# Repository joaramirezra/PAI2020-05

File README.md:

# Proyecto Respirador unal
**Version :** 1.0

**Descripcion :** Durante la epidemia del covid-19, el mundo afronta un sin fin de desafios entre ellos el preservar la mayor cantidad de vidas posibles,Esta infeccion suelen contar con fiebre y síntomas respiratorios (tos y disnea o dificultad para respirar). En los casos más graves, pueden causar neumonía, síndrome respiratorio agudo severo, insuficiencia renal e, incluso, la muerte. 

Dicho lo anterior, este proyecto contiene informacion basica para Construir un respirador mecanico de bajo costo para asistir a los pacientes con sindromes respiratorios como se muestra en el siguiente video 

### Requerimientos 

* [KiCad 5.1.5](https://www.kicad-pcb.org/download/)
* [ARDUINO 1.8.12 ](https://www.arduino.cc/en/main/software)
* [Inventor 2019](https://knowledge.autodesk.com/support/inventor/learn-explore/caas/CloudHelp/cloudhelp/2019/ENU/Inventor-WhatsNew/files/GUID-4FBBFD8B-4076-4A08-9CCF-71C4B3FF533E-htm.html)
* [matlab 2018b](https://www.mathworks.com/products/new_products/release2018b.html)

### Colaboladores :
- [Johan Ramirez](https://github.com/joaramirezra)
- [Sebastian Realpe](https://github.com/GitSRealpe)
- [Jurgen krejci](https://github.com/JurgenHK)
- Dario Gutierrez
- Pedro Cardenas
- Ricardo Ramirez

### License

- [Creative commons 4.0 ](https://creativecommons.org/licenses/by/4.0)

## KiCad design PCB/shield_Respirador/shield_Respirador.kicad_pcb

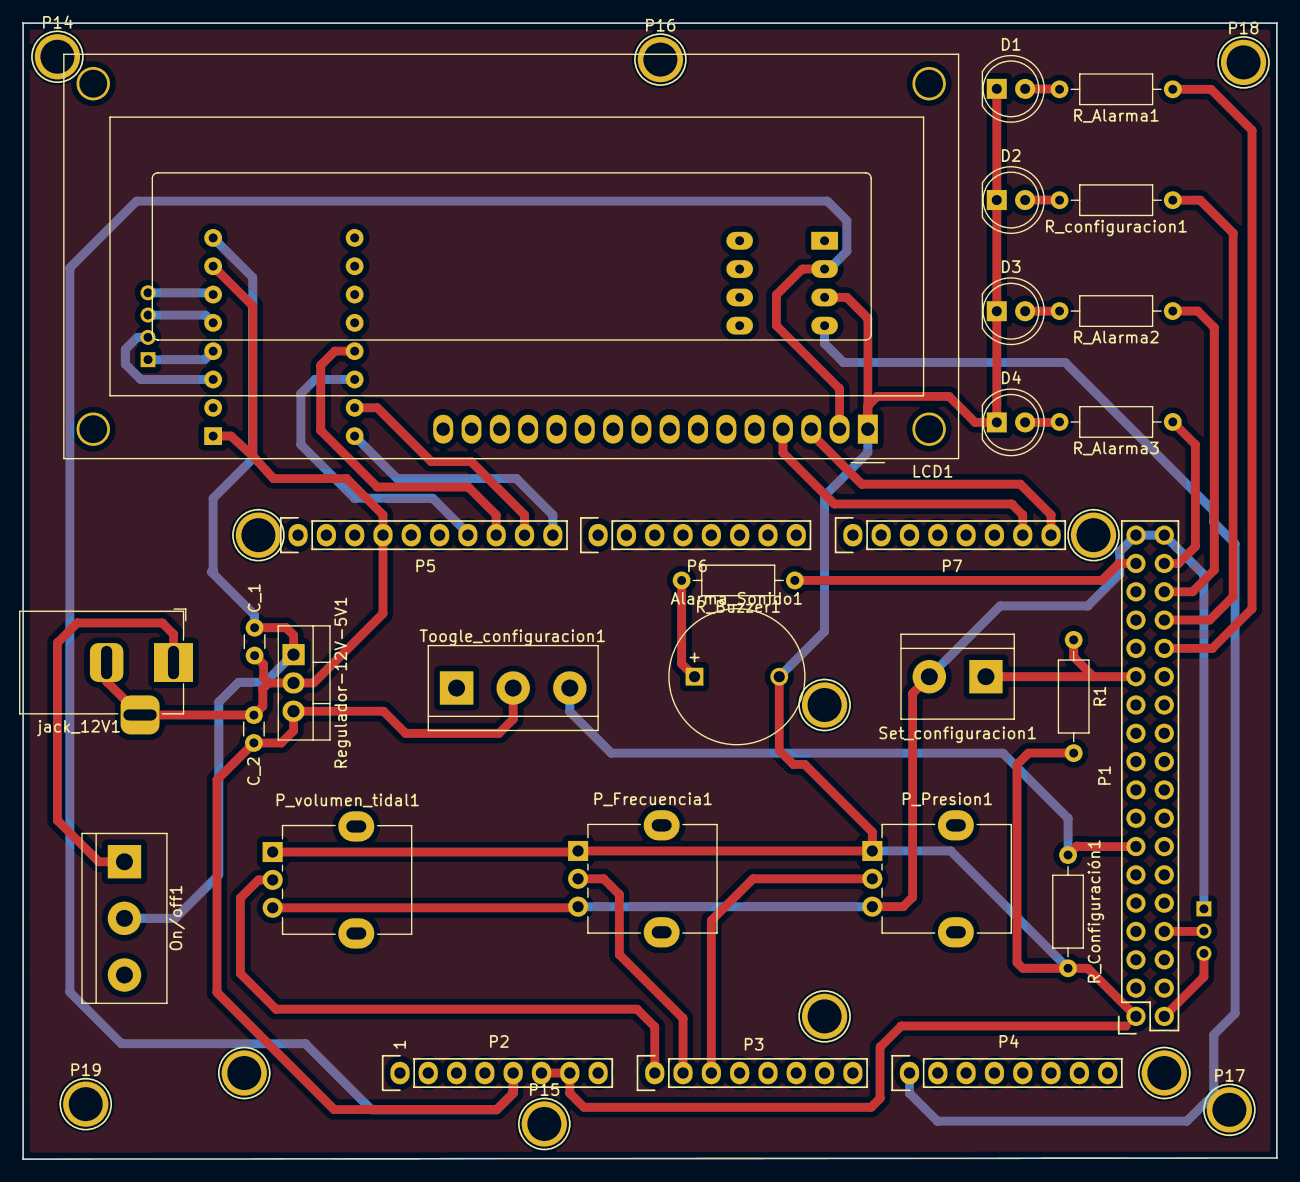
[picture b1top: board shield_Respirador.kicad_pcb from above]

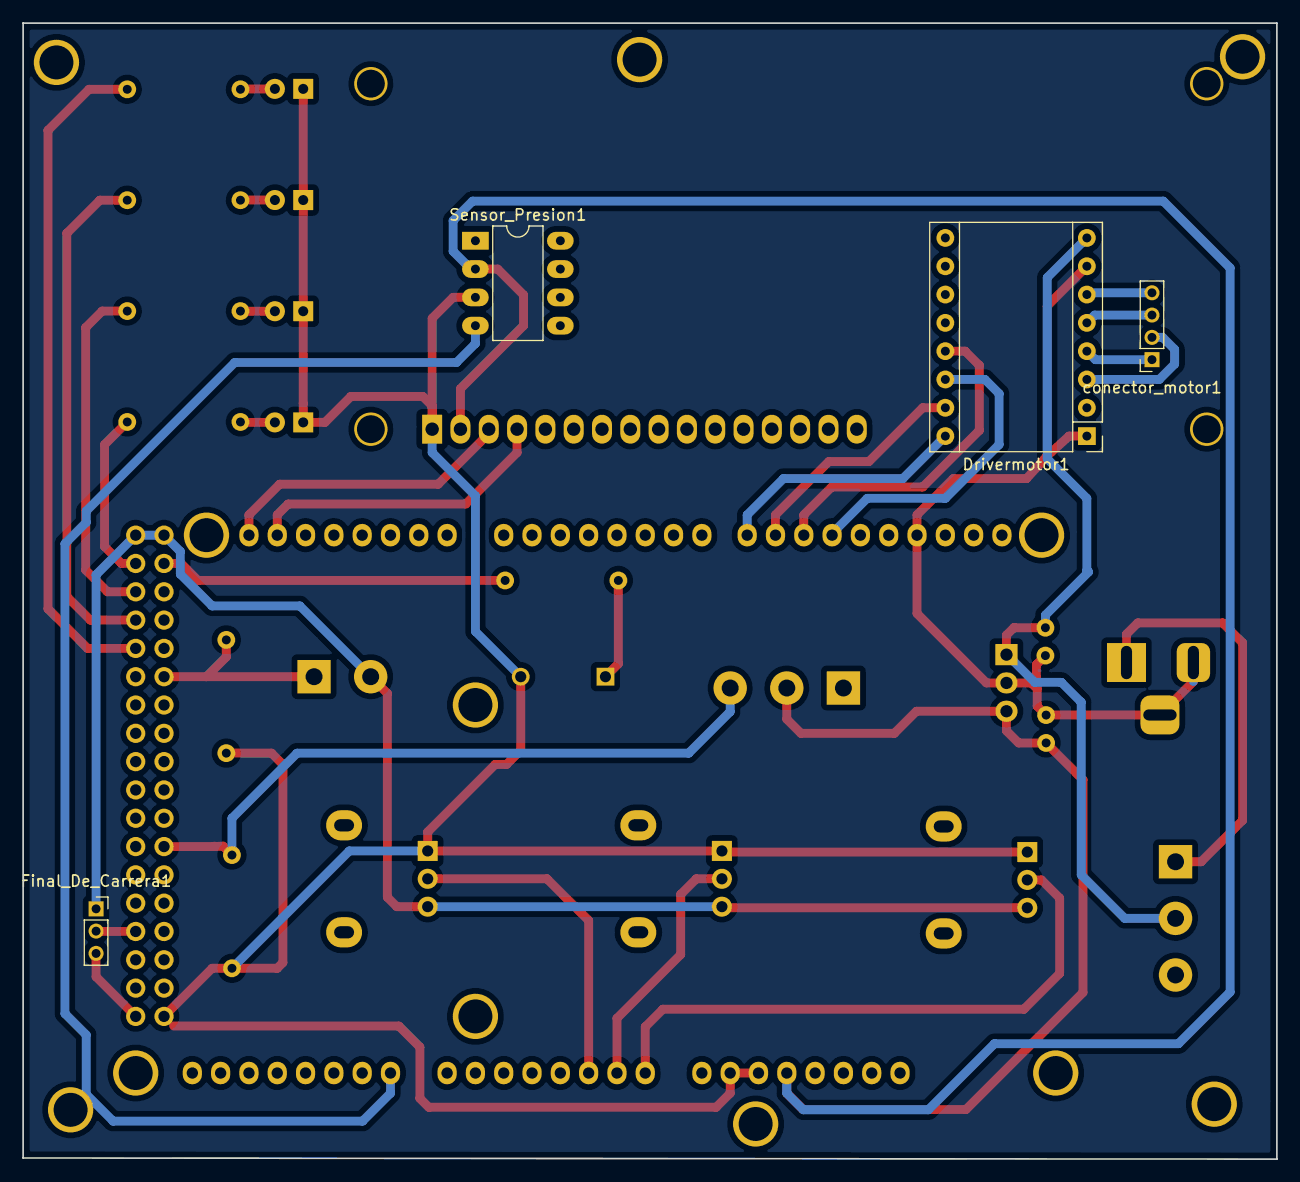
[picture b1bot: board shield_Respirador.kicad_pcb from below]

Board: 2 copper layers, 112.5 x 101.9 mm, 46 parts (4 on the bottom side), 31 nets.

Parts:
Alarma_Sonido1: Buzzer; MagneticBuzzer_ProSignal_ABI-009-RC
C_1: 0.33uf; C_Disc_D3.0mm_W1.6mm_P2.50mm
C_2: 0.1uf; C_Disc_D3.0mm_W1.6mm_P2.50mm
D1, D2, D3, D4: L_Alarma; LED_D5.0mm
Drivermotor1: DRV8825; Pololu_Breakout-16_15.2x20.3mm
Final_De_Carrera1: Conn_01x03_Female; PinSocket_1x03_P2.00mm_Vertical
LCD1: WC1602A
On/off1: SW_DPDT_x2; TerminalBlock_bornier-3_P5.08mm
P1: Digital; Socket_Strip_Arduino_2x18
P2: Power; Socket_Strip_Arduino_1x08
P3, P4: Analog; Socket_Strip_Arduino_1x08
P5: PWM; Socket_Strip_Arduino_1x10
P6: PWM; Socket_Strip_Arduino_1x08
P7: Communication; Socket_Strip_Arduino_1x08
P8, P9, P10, P11, P12, P13, P14, P15, P16, P17, P18, P19: CONN_01X01; Arduino_1pin
P_Frecuencia1: 5k; Potentiometer_Alpha_RD901F-40-00D_Single_Vertical
P_Presion1: 5k; Potentiometer_Alpha_RD901F-40-00D_Single_Vertical
P_volumen_tidal1: 5k; Potentiometer_Alpha_RD901F-40-00D_Single_Vertical
R1: R; R_Axial_DIN0207_L6.3mm_D2.5mm_P10.16mm_Horizontal
R_Alarma1, R_Alarma2, R_Alarma3: 220; R_Axial_DIN0207_L6.3mm_D2.5mm_P10.16mm_Horizontal
R_Buzzer1: 220; R_Axial_DIN0207_L6.3mm_D2.5mm_P10.16mm_Horizontal
R_Configuración1: 220; R_Axial_DIN0207_L6.3mm_D2.5mm_P10.16mm_Horizontal
R_configuracion1: 220; R_Axial_DIN0207_L6.3mm_D2.5mm_P10.16mm_Horizontal
Regulador-12V-5V1: L7805; TO-220-3_Vertical
Sensor_Presion1: MPXA6115A; DIP-8_W7.62mm_LongPads
Set_configuracion1: SW_Push; TerminalBlock_bornier-2_P5.08mm
Toogle_configuracion1: SW_Push_SPDT; TerminalBlock_bornier-3_P5.08mm
conector_motor1: Conn_01x04_Female; PinSocket_1x04_P2.00mm_Vertical
jack_12V1: Alimentacion_12V; BarrelJack_Horizontal

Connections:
+5V: C_2.1, Final_De_Carrera1.1, LCD1.2, P1.35, P1.36, P2.5, P_Frecuencia1.3, P_Presion1.3, P_volumen_tidal1.3, Regulador-12V-5V1.3, Sensor_Presion1.2, Set_configuracion1.2, Toogle_configuracion1.2
+12V: C_1.1, Drivermotor1.8, On/off1.2, Regulador-12V-5V1.1
/8(**): Drivermotor1.16, P5.10
/9(**): Drivermotor1.15, P5.9
/10(**): Drivermotor1.13, P5.8
/11(**): Drivermotor1.14, P5.7
/20(SDA): LCD1.4, P7.7
/21(SCL): LCD1.3, P7.8
/22: P1.33, R_Buzzer1.1
/23: P1.34, R_Alarma3.1
/25: P1.32, R_Alarma2.1
/27: P1.30, R_configuracion1.1
/29: P1.28, R_Alarma1.1
/30: P1.25, R1.1, Set_configuracion1.1
/42: P1.13, R_Configuración1.1, Toogle_configuracion1.3
/49: Final_De_Carrera1.2, P1.8
/A0: P3.1, P_volumen_tidal1.2
/A1: P3.2, P_Frecuencia1.2
/A2: P3.3, P_Presion1.2
/A8: P4.1, Sensor_Presion1.4
GND: Alarma_Sonido1.2, C_1.2, C_2.2, D1.1, D2.1, D3.1, D4.1, Drivermotor1.1, Drivermotor1.7, Final_De_Carrera1.3, LCD1.1, P1.1, P1.2, P2.6, P2.7, P5.4, P_Frecuencia1.1, P_Presion1.1, P_volumen_tidal1.1, R1.2, R_Configuración1.2, Regulador-12V-5V1.2, Sensor_Presion1.3, jack_12V1.2, jack_12V1.3
unnamed: Alarma_Sonido1.1, R_Buzzer1.2
unnamed: D1.2, R_Alarma1.2
unnamed: D2.2, R_configuracion1.2
unnamed: D3.2, R_Alarma2.2
unnamed: D4.2, R_Alarma3.2
unnamed: Drivermotor1.3, conector_motor1.2
unnamed: Drivermotor1.4, conector_motor1.1
unnamed: Drivermotor1.5, conector_motor1.3
unnamed: Drivermotor1.6, conector_motor1.4
unnamed: On/off1.1, jack_12V1.1

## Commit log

2020-03-29 version 0
2020-03-30 Verison 0
2020-03-30 Se agrega el codigo que permite que la lcd funcione en el arduino Mega, ya se comprobo su funcionamiento
2020-04-04 version 0.1 , se crea el main y la clase paciente
2020-04-04 version 0.2 se configuro la lectrura de los potenciometros por medio de la creacion de una libreria
2020-04-04 version 0.3 Se configuro el lcd y permite visualizar valores
2020-04-04 version 0.31 las conexiones provadas ya estan en esquematico
2020-04-05 Diseño esquematico para presenstacion
2020-04-05 version 0.35 se adiciona el archivo step
2020-04-07 version 3.6 segunda version pcb
2020-04-07 version 0.4
2020-04-07 version 0.41 Esquematico terminado y irganizado
2020-04-08 version 0.5 se termina esquematico y renderizacion
2020-04-08 version 0.55 interfaz basica funcionando
2020-04-12 version 0.6 Prueba de motor validada
2020-04-13 version 0.61 inicio Documentacion
2020-04-13 Version 0.6 se recupera electronica
2020-04-13 Version 0.65 Recuperada
2020-04-13 Version 0.67
    Se agrega documentacion del respirador hasta el momento
2020-04-13 v 6.6 Pruebas
2020-04-13 pruebas
2020-04-13 Repo organizado
2020-04-14 Versión 0.8 Perfiles de velocidad
2020-04-14 v 0.81 Pruebas en maquina
2020-04-14 prueba
2020-04-14 Version 0.9 Funcionando en vacio
2020-04-14 Version 0.91 Funcionando en vacio
2020-04-14 Version 1.0 funcionando!
2020-04-17 CAD/Simulación
    Se añaden los archivos CAD en su ultima versión, y se añade el Script de la simulación de perfiles de motor en Matlab
2020-05-04 version 1.01
2020-05-06 V1.2 sensorica en un solo micro
2020-05-09 v1.6 codigo funcionando solo falta documentar
2020-05-11 V1.2
